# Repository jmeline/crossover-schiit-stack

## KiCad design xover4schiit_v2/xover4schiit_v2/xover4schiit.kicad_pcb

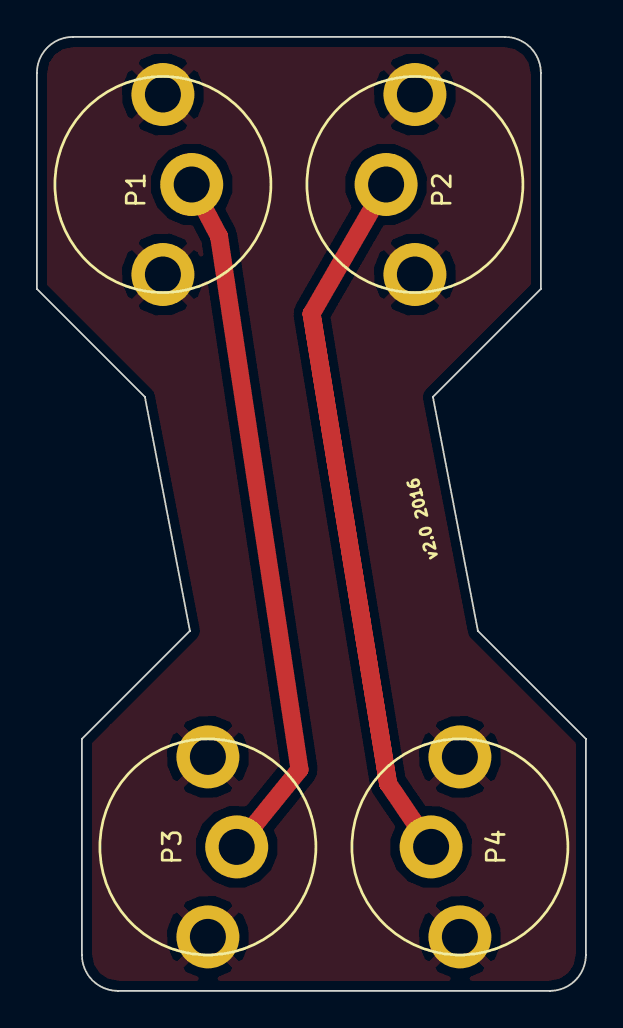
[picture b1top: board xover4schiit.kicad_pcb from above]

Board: 2 copper layers, 30.5 x 53.0 mm, 4 parts (0 on the bottom side), 3 nets.

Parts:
P1, P2, P3, P4: bnc_pcb

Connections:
/A: P1.1, P3.1
/B: P2.1, P4.1
GND: P1.2, P2.2, P3.2, P4.2

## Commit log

2020-05-12 Add v2 xover4schiit kicad and gerber files
